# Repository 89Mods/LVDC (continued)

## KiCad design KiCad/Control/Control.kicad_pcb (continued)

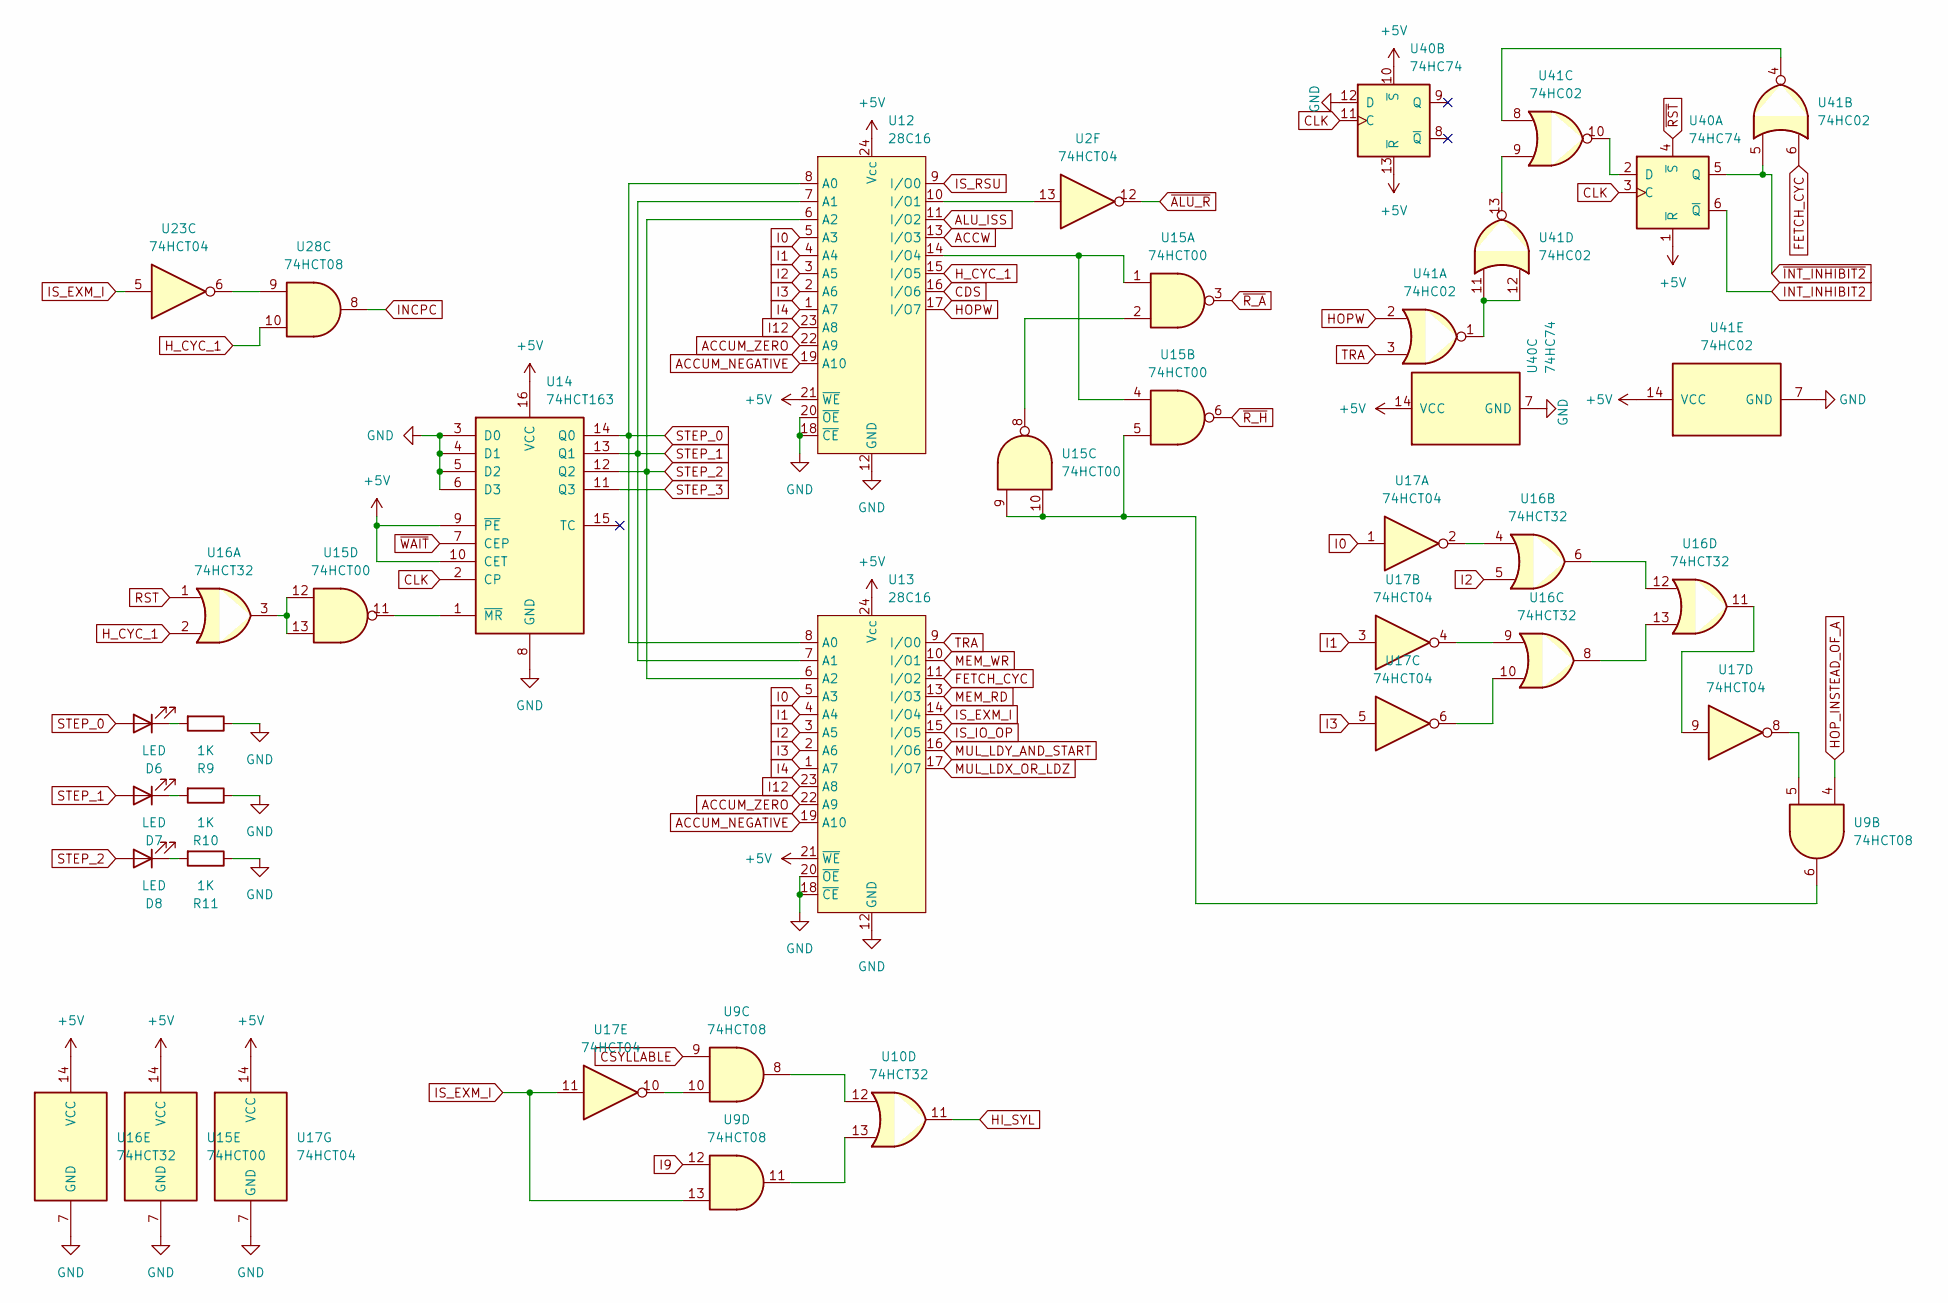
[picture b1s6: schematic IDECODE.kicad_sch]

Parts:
D6, D7, D8: LED; LED_1206_3216Metric_Pad1.42x1.75mm_HandSolder
R9, R10, R11: 1K; R_1206_3216Metric_Pad1.30x1.75mm_HandSolder
U2, U17, U23: 74HCT04; SO-14_3.9x8.65mm_P1.27mm
U9, U28: 74HCT08; SO-14_3.9x8.65mm_P1.27mm
U10, U16: 74HCT32; SO-14_3.9x8.65mm_P1.27mm
U12, U13: 28C16; DIP-24_W15.24mm_Socket
U14: 74HCT163; DIP-16_W7.62mm
U15: 74HCT00; SO-14_3.9x8.65mm_P1.27mm
U40: 74HC74; SO-14_3.9x8.65mm_P1.27mm
U41: 74HC02; SO-14_3.9x8.65mm_P1.27mm

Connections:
+5V: U12.21 (~WE), U12.24 (Vcc), U13.21 (~WE), U13.24 (Vcc), U14.9 (~PE), U14.10 (CET), U14.16 (VCC), U15.14 (VCC), U16.14 (VCC), U17.14 (VCC), U40.1 (~R), U40.10 (~S), U40.13 (~R), U40.14 (VCC), U41.14 (VCC); also elsewhere on the board
ACCUM_NEGATIVE: U12.19 (A10), U13.19 (A10); also elsewhere on the board
ACCUM_ZERO: U12.22 (A9), U13.22 (A9); also elsewhere on the board
ACCW: U12.13 (I/O3); also elsewhere on the board
ALU_ISS: U12.11 (I/O2); also elsewhere on the board
CDS: U12.16 (I/O6); also elsewhere on the board
CLK: U14.2 (CP), U40.3 (C), U40.11 (C); also elsewhere on the board
CSYLLABLE: U9.9; also elsewhere on the board
FETCH_CYC: U13.11 (I/O2), U41.6; also elsewhere on the board
GND: R9.1, R10.1, R11.1, U12.12 (GND), U12.18 (~CE), U12.20 (~OE), U13.12 (GND), U13.18 (~CE), U13.20 (~OE), U14.3 (D0), U14.4 (D1), U14.5 (D2), U14.6 (D3), U14.8 (GND), U15.7 (GND), U16.7 (GND), U17.7 (GND), U40.7 (GND), U40.12 (D), U41.7 (GND); also elsewhere on the board
HI_SYL: U10.11; also elsewhere on the board
HOPW: U12.17 (I/O7), U41.2; also elsewhere on the board
HOP_INSTEAD_OF_A: U9.4; also elsewhere on the board
H_CYC_1: U12.15 (I/O5), U16.2, U28.10; also elsewhere on the board
I0: U12.5 (A3), U13.5 (A3), U17.1; also elsewhere on the board
I1: U12.4 (A4), U13.4 (A4), U17.3; also elsewhere on the board
I2: U12.3 (A5), U13.3 (A5), U16.5; also elsewhere on the board
I3: U12.2 (A6), U13.2 (A6), U17.5; also elsewhere on the board
I4: U12.1 (A7), U13.1 (A7); also elsewhere on the board
I9: U9.12; also elsewhere on the board
I12: U12.23 (A8), U13.23 (A8); also elsewhere on the board
INCPC: U28.8; also elsewhere on the board
INT_INHIBIT2: U40.6 (~Q); also elsewhere on the board
IS_EXM_I: U9.13, U13.14 (I/O4), U17.11, U23.5; also elsewhere on the board
IS_IO_OP: U13.15 (I/O5); also elsewhere on the board
IS_RSU: U12.9 (I/O0); also elsewhere on the board
MEM_RD: U13.13 (I/O3); also elsewhere on the board
MEM_WR: U13.10 (I/O1); also elsewhere on the board
MUL_LDX_OR_LDZ: U13.17 (I/O7); also elsewhere on the board
MUL_LDY_AND_START: U13.16 (I/O6); also elsewhere on the board
unnamed: D6.1 (K), R9.2
unnamed: D7.1 (K), R10.2
unnamed: D8.1 (K), R11.2
unnamed: U9.8, U10.12
unnamed: U9.11, U10.13
unnamed: U2.13, U12.10 (I/O1)
unnamed: U12.14 (I/O4), U15.1, U15.4
unnamed: U14.1 (~MR), U15.11
unnamed: U15.2, U15.8
unnamed: U9.6, U15.5, U15.9, U15.10
unnamed: U15.12, U15.13, U16.3
unnamed: U16.4, U17.2
unnamed: U16.9, U17.4
unnamed: U16.10, U17.6
unnamed: U16.11, U17.9
unnamed: U16.6, U16.12
unnamed: U16.8, U16.13
unnamed: U9.5, U17.8
unnamed: U9.10, U17.10
unnamed: U23.6, U28.9
unnamed: U40.2 (D), U41.10
unnamed: U41.1, U41.11, U41.12
unnamed: U41.4, U41.8
unnamed: U41.9, U41.13
RST: U16.1; also elsewhere on the board
STEP_0: D6.2 (A), U12.8 (A0), U13.8 (A0), U14.14 (Q0)
STEP_1: D7.2 (A), U12.7 (A1), U13.7 (A1), U14.13 (Q1)
STEP_2: D8.2 (A), U12.6 (A2), U13.6 (A2), U14.12 (Q2); also elsewhere on the board
STEP_3: U14.11 (Q3)
TRA: U13.9 (I/O0), U41.3; also elsewhere on the board
~ALU_R: U2.12; also elsewhere on the board
~INT_INHIBIT2: U40.5 (Q), U41.5
~RST: U40.4 (~S); also elsewhere on the board
~R_A: U15.3; also elsewhere on the board
~R_H: U15.6; also elsewhere on the board
~WAIT: U14.7 (CEP); also elsewhere on the board

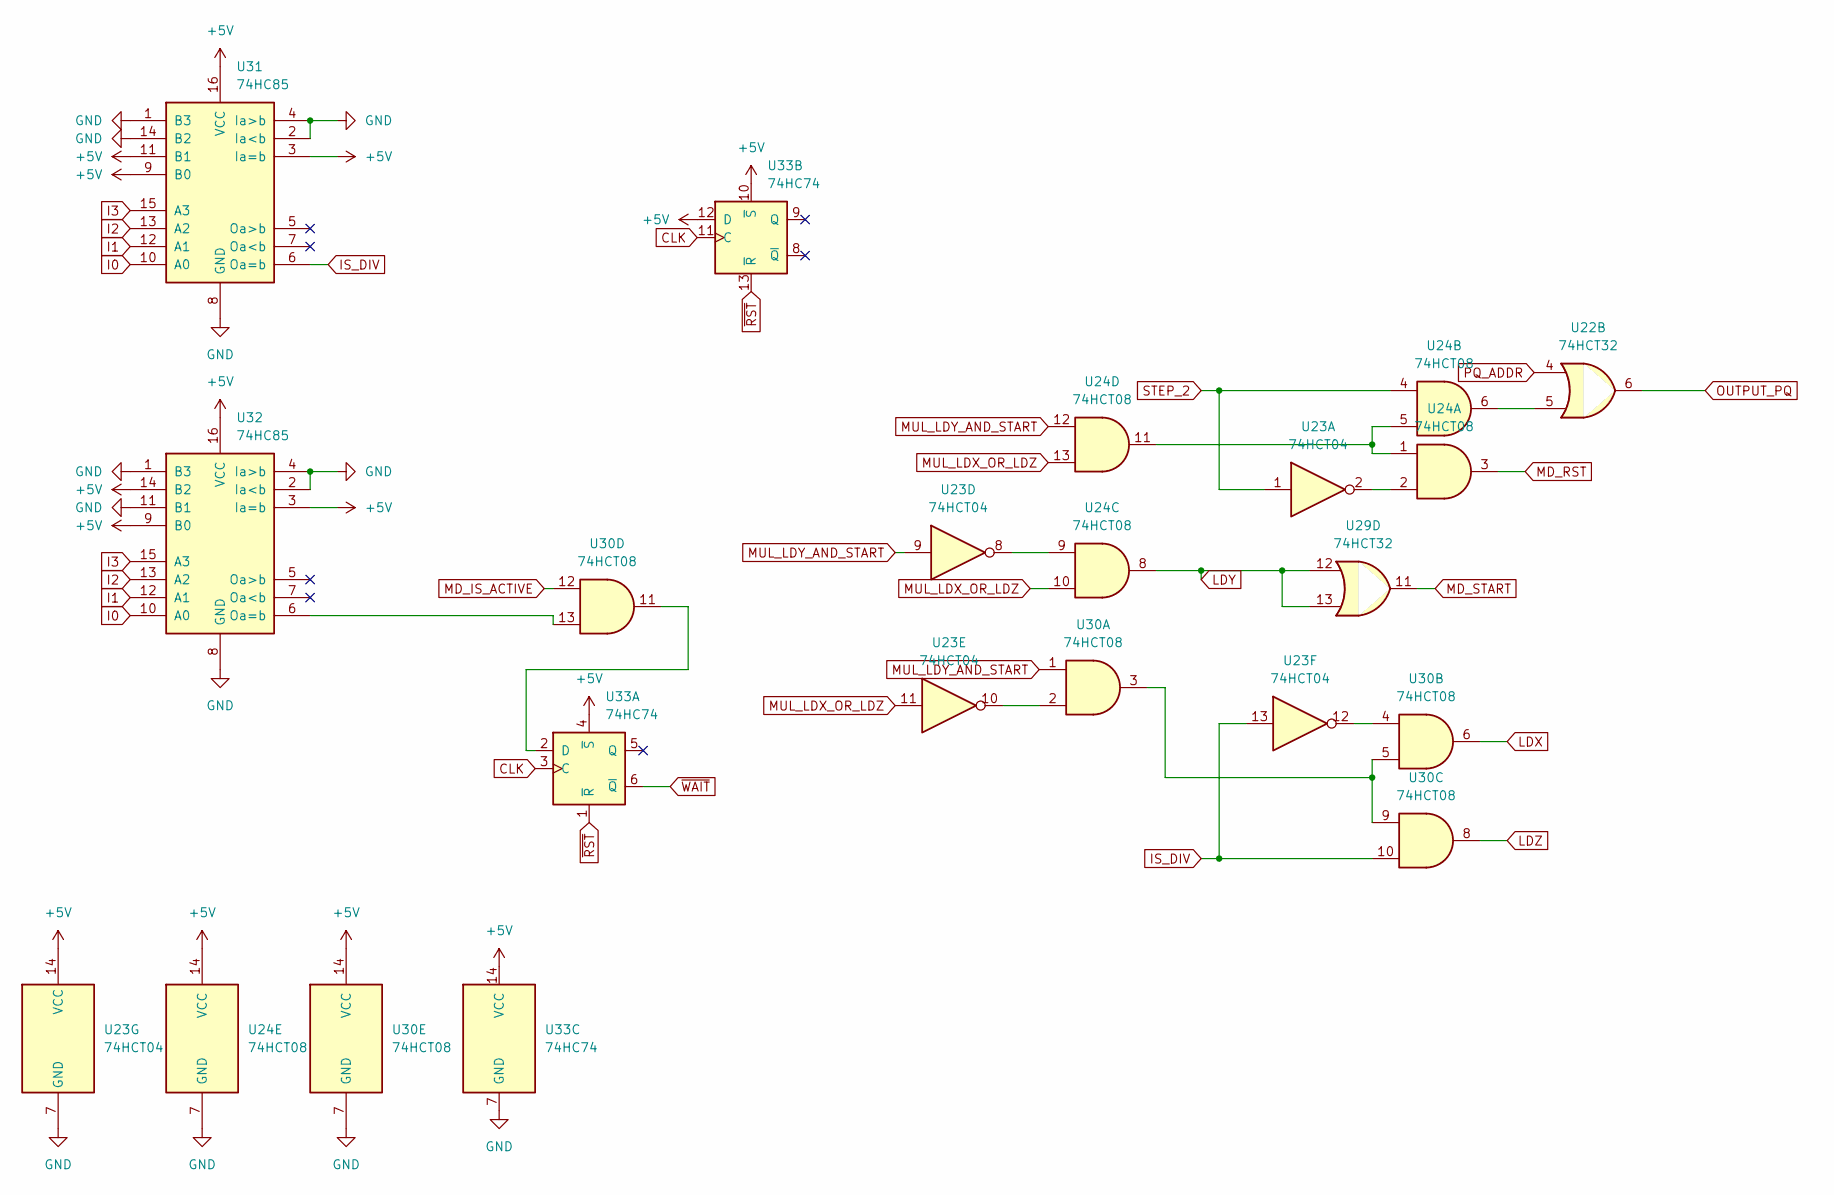
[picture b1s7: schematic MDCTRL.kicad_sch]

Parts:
U22, U29: 74HCT32; SO-14_3.9x8.65mm_P1.27mm
U23: 74HCT04; SO-14_3.9x8.65mm_P1.27mm
U24, U30: 74HCT08; SO-14_3.9x8.65mm_P1.27mm
U31, U32: 74HC85; DIP-16_W7.62mm
U33: 74HC74; SO-14_3.9x8.65mm_P1.27mm

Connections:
+5V: U23.14 (VCC), U24.14 (VCC), U30.14 (VCC), U31.3 (Ia=b), U31.9 (B0), U31.11 (B1), U31.16 (VCC), U32.3 (Ia=b), U32.9 (B0), U32.14 (B2), U32.16 (VCC), U33.4 (~S), U33.10 (~S), U33.12 (D), U33.14 (VCC); also elsewhere on the board
CLK: U33.3 (C), U33.11 (C); also elsewhere on the board
GND: U23.7 (GND), U24.7 (GND), U30.7 (GND), U31.1 (B3), U31.2 (Ia<b), U31.4 (Ia>b), U31.8 (GND), U31.14 (B2), U32.1 (B3), U32.2 (Ia<b), U32.4 (Ia>b), U32.8 (GND), U32.11 (B1), U33.7 (GND); also elsewhere on the board
I0: U31.10 (A0), U32.10 (A0); also elsewhere on the board
I1: U31.12 (A1), U32.12 (A1); also elsewhere on the board
I2: U31.13 (A2), U32.13 (A2); also elsewhere on the board
I3: U31.15 (A3), U32.15 (A3); also elsewhere on the board
IS_DIV: U23.13, U30.10, U31.6 (Oa=b); also elsewhere on the board
LDX: U30.6; also elsewhere on the board
LDY: U24.8, U29.12, U29.13; also elsewhere on the board
LDZ: U30.8; also elsewhere on the board
MD_IS_ACTIVE: U30.12; also elsewhere on the board
MD_RST: U24.3; also elsewhere on the board
MD_START: U29.11; also elsewhere on the board
MUL_LDX_OR_LDZ: U23.11, U24.10, U24.13; also elsewhere on the board
MUL_LDY_AND_START: U23.9, U24.12, U30.1; also elsewhere on the board
unnamed: U22.5, U24.6
unnamed: U23.2, U24.2
unnamed: U23.8, U24.9
unnamed: U23.10, U30.2
unnamed: U23.12, U30.4
unnamed: U24.1, U24.5, U24.11
unnamed: U30.3, U30.5, U30.9
unnamed: U30.13, U32.6 (Oa=b)
unnamed: U30.11, U33.2 (D)
OUTPUT_PQ: U22.6; also elsewhere on the board
PQ_ADDR: U22.4; also elsewhere on the board
STEP_2: U23.1, U24.4; also elsewhere on the board
~RST: U33.1 (~R), U33.13 (~R); also elsewhere on the board
~WAIT: U33.6 (~Q); also elsewhere on the board

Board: 4 copper layers, 81 parts (0 on the bottom side), 202 nets, no tracks yet.

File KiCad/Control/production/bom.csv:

Designator,Footprint,Quantity,Value,LCSC Part #
"C1, C10, C11, C12, C13, C7, C8, C9",0805,8,100nF,
"C2, C3, C4, C5, C6",CP_Radial_D4.0mm_P2.00mm,5,10µF,
"D1, D2, D3, D4, D5, D6, D7, D8",1206,8,LED,
J1,PinHeader_2x22_P2.54mm_Vertical,1,TO_BACKPLANE,
J2,PinHeader_2x04_P2.54mm_Vertical,1,TO_ALU,
J3,PinHeader_2x06_P2.54mm_Vertical,1,TO_MEMORY,
J4,PinHeader_2x06_P2.54mm_Vertical,1,TO_REGISTERS,
J5,PinHeader_2x04_P2.54mm_Vertical,1,TO_MULDIV,
"J6, J7, J8",PinHeader_1x01_P2.54mm_Vertical,3,Conn_01x01,
"R1, R10, R11, R2, R6, R8, R9",1206,7,1K,
R3,1206,1,4.7K,
"R4, R5, R7",1206,3,15K,
"U1, U7",SO-20_12.8x7.5mm_P1.27mm,2,74HC574,
"U10, U16, U22, U29",SO-14_3.9x8.65mm_P1.27mm,4,74HCT32,
"U11, U21, U24, U25, U28, U30, U9",SO-14_3.9x8.65mm_P1.27mm,7,74HCT08,
"U12, U13",DIP-24_W15.24mm_Socket,2,28C16,
U14,DIP-16_W7.62mm,1,74HCT163,
U15,SO-14_3.9x8.65mm_P1.27mm,1,74HCT00,
"U17, U2, U23",SO-14_3.9x8.65mm_P1.27mm,3,74HCT04,
"U18, U19, U26, U27",SO-14_3.9x8.65mm_P1.27mm,4,74HCT74,
"U20, U3, U36, U37, U38, U39, U4, U5, U6, U8",SO-16_3.9x9.9mm_P1.27mm,10,74HCT157,
"U31, U32",DIP-16_W7.62mm,2,74HC85,
U33,SO-14_3.9x8.65mm_P1.27mm,1,74HC74,
U34,SO-20_12.8x7.5mm_P1.27mm,1,74HC688,
U35,SO-14_3.9x8.65mm_P1.27mm,1,74HC00,

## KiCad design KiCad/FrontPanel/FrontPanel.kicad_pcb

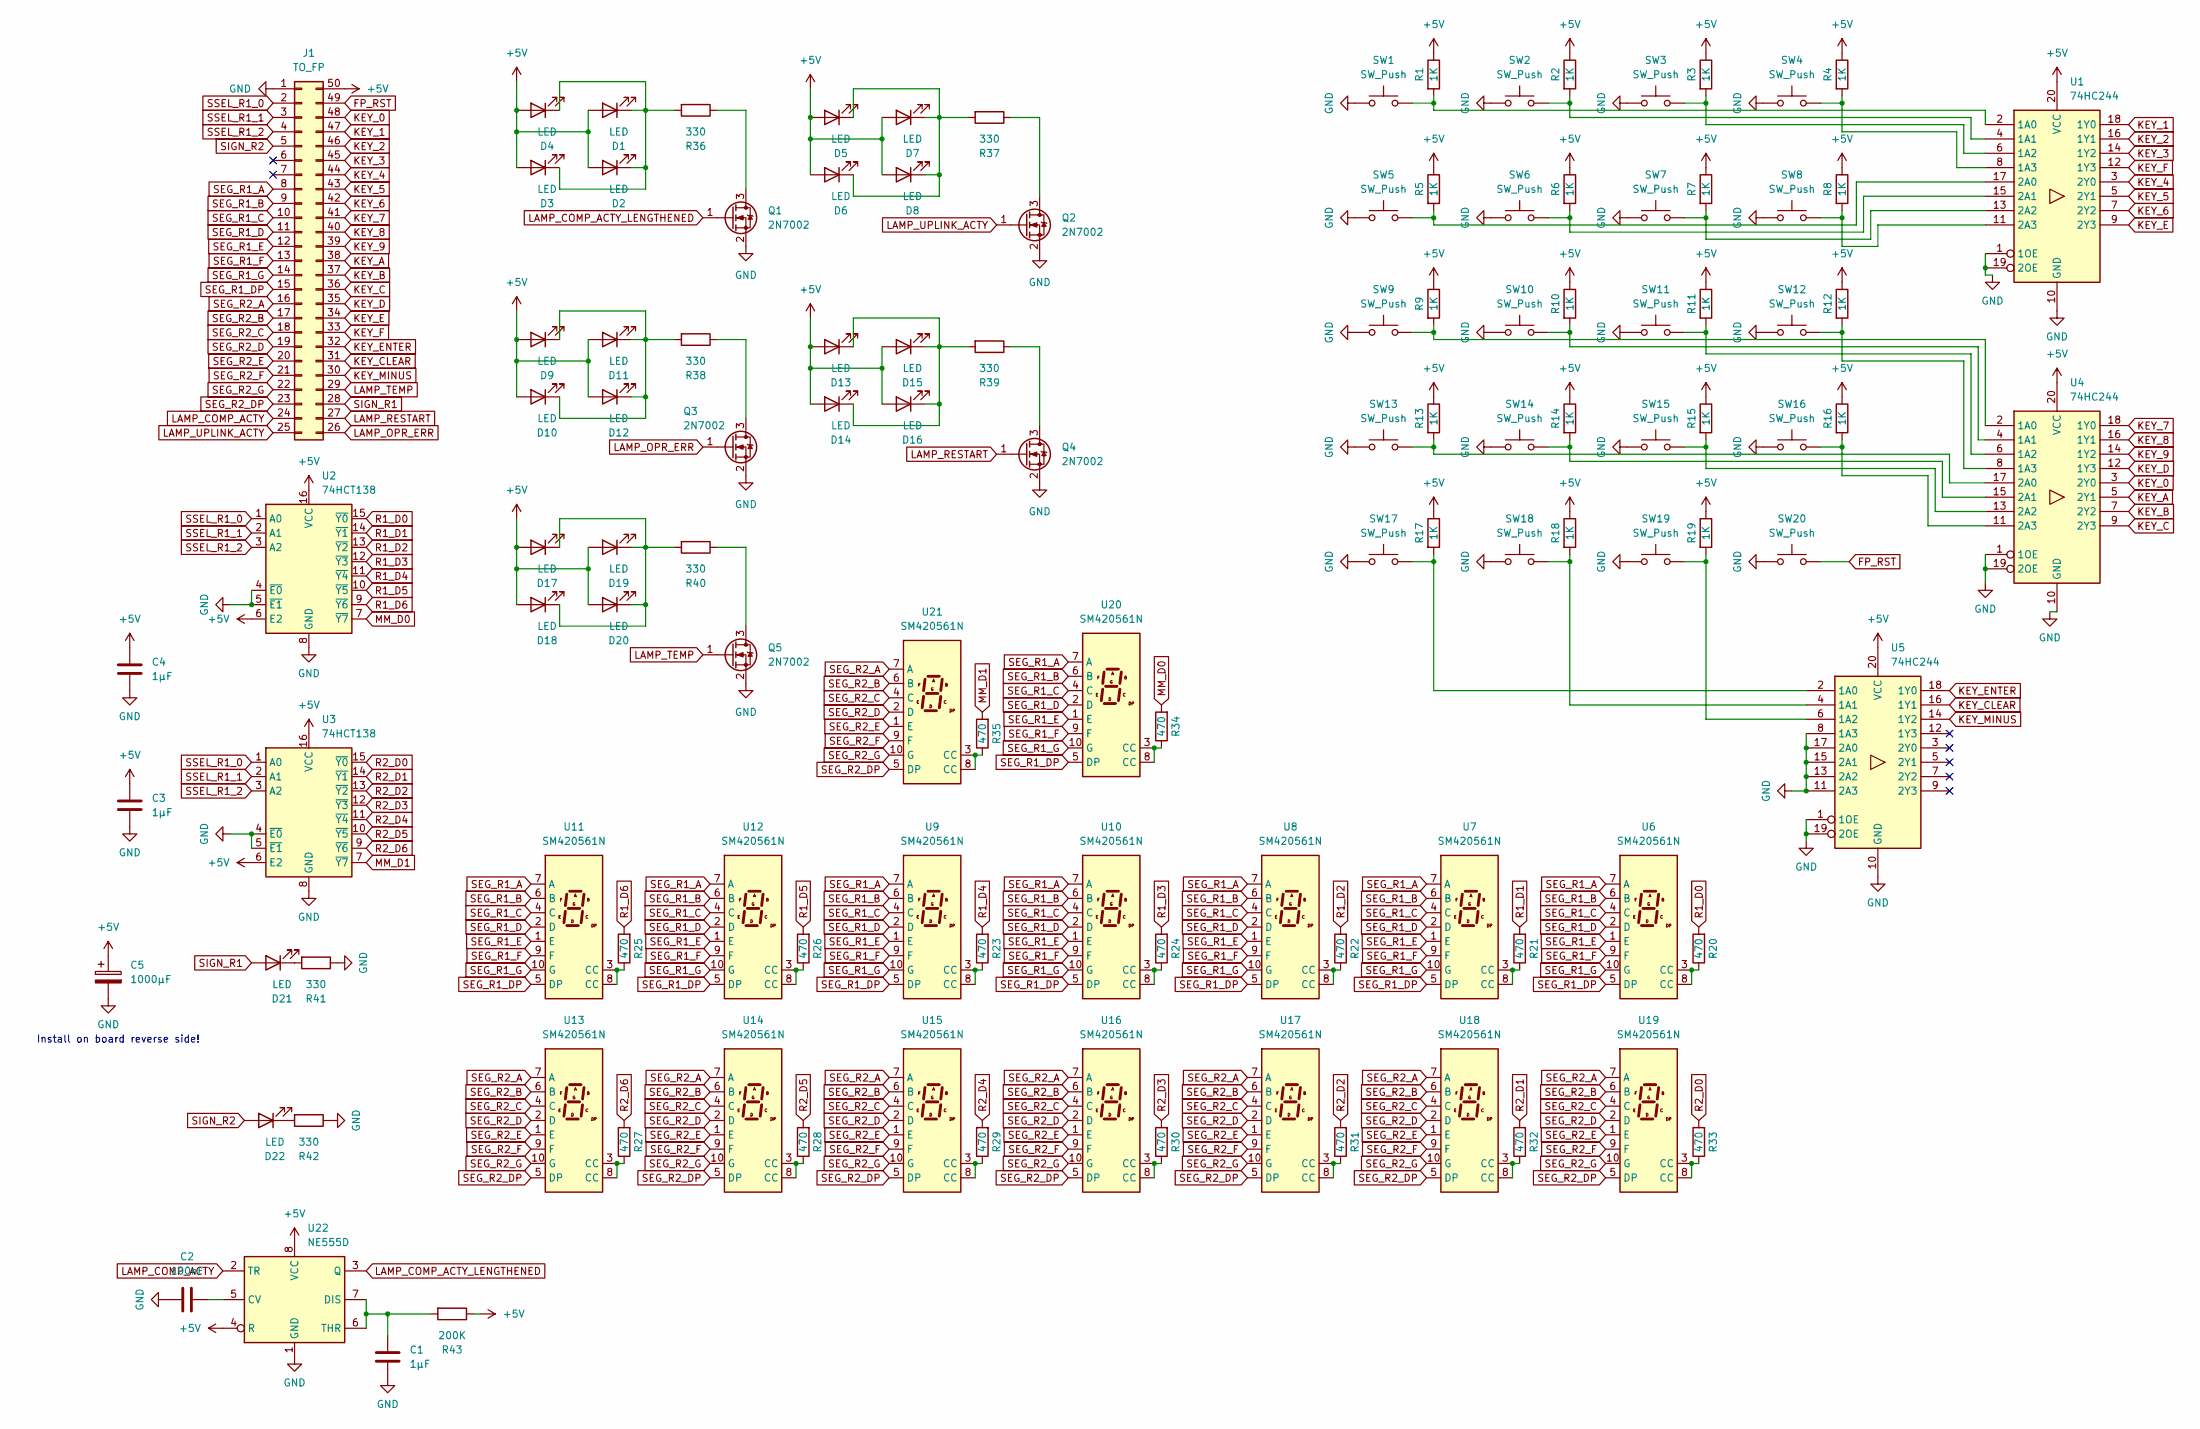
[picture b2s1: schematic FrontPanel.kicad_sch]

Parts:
C1, C3, C4: 1µF; C_0805_2012Metric_Pad1.18x1.45mm_HandSolder
C2: 100nF; C_0805_2012Metric_Pad1.18x1.45mm_HandSolder
C5: 1000µF; CP_Radial_D6.3mm_P2.50mm
D1, D2, D3, D4, D5, D6, D7, D8, D9, D10, D11, D12, D13, D14, D15, D16, D17, D18, D19, D20: LED; LED_1206_3216Metric_Pad1.42x1.75mm_HandSolder
D21, D22: LED; LED_D5.0mm
J1: TO_FP; PinHeader_2x25_P2.54mm_Vertical
Q1, Q2, Q3, Q4, Q5: 2N7002; SOT-23
R1, R2, R3, R4, R5, R6, R7, R8, R9, R10, R11, R12, R13, R14, R15, R16, R17, R18, R19: 1K; R_1206_3216Metric_Pad1.30x1.75mm_HandSolder
R20, R21, R22, R23, R24, R25, R26, R27, R28, R29, R30, R31, R32, R33, R34, R35: 470; R_1206_3216Metric_Pad1.30x1.75mm_HandSolder
R36, R37, R38, R39, R40, R41, R42: 330; R_1206_3216Metric_Pad1.30x1.75mm_HandSolder
R43: 200K; R_1206_3216Metric_Pad1.30x1.75mm_HandSolder
SW1, SW2, SW3, SW4, SW5, SW6, SW7, SW8, SW9, SW10, SW11, SW12, SW13, SW14, SW15, SW16, SW17, SW18, SW19, SW20: SW_Push; SW_Cherry_MX_1.00u_PCB
U1, U4, U5: 74HC244; SO-20_12.8x7.5mm_P1.27mm
U2, U3: 74HCT138; SO-16_3.9x9.9mm_P1.27mm
U6, U7, U8, U9, U10, U11, U12, U13, U14, U15, U16, U17, U18, U19, U20, U21: SM420561N; 7SegmentLED_LTS6760_LTS6780
U22: NE555D; SOIC-8_3.9x4.9mm_P1.27mm

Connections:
+5V: C3.2, C4.2, C5.1, D1.2 (A), D2.2 (A), D3.2 (A), D4.2 (A), D5.2 (A), D6.2 (A), D7.2 (A), D8.2 (A), D9.2 (A), D10.2 (A), D11.2 (A), D12.2 (A), D13.2 (A), D14.2 (A), D15.2 (A), D16.2 (A), D17.2 (A), D18.2 (A), D19.2 (A), D20.2 (A), J1.50, R1.1, R2.1, R3.1, R4.1, R5.1, R6.1, R7.1, R8.1, R9.1, R10.1, R11.1, R12.1, R13.1, R14.1, R15.1, R16.1, R17.1, R18.1, R19.1, R43.1, U1.20 (VCC), U2.6 (E2), U2.16 (VCC), U3.6 (E2), U3.16 (VCC), U4.20 (VCC), U5.20 (VCC), U22.4 (R), U22.8 (VCC)
FP_RST: J1.49, SW20.2
GND: C1.1, C2.2, C3.1, C4.1, C5.2, J1.1, Q1.2 (S), Q2.2 (S), Q3.2 (S), Q4.2 (S), Q5.2 (S), R41.1, R42.1, SW1.1, SW2.1, SW3.1, SW4.1, SW5.1, SW6.1, SW7.1, SW8.1, SW9.1, SW10.1, SW11.1, SW12.1, SW13.1, SW14.1, SW15.1, SW16.1, SW17.1, SW18.1, SW19.1, SW20.1, U1.1 (1OE), U1.10 (GND), U1.19 (2OE), U2.4 (~E0), U2.5 (~E1), U2.8 (GND), U3.4 (~E0), U3.5 (~E1), U3.8 (GND), U4.1 (1OE), U4.10 (GND), U4.19 (2OE), U5.1 (1OE), U5.8 (1A3), U5.10 (GND), U5.11 (2A3), U5.13 (2A2), U5.15 (2A1), U5.17 (2A0), U5.19 (2OE), U22.1 (GND)
KEY_0: J1.48, U4.3 (2Y0)
KEY_1: J1.47, U1.18 (1Y0)
KEY_2: J1.46, U1.16 (1Y1)
KEY_3: J1.45, U1.14 (1Y2)
KEY_4: J1.44, U1.3 (2Y0)
KEY_5: J1.43, U1.5 (2Y1)
KEY_6: J1.42, U1.7 (2Y2)
KEY_7: J1.41, U4.18 (1Y0)
KEY_8: J1.40, U4.16 (1Y1)
KEY_9: J1.39, U4.14 (1Y2)
KEY_A: J1.38, U4.5 (2Y1)
KEY_B: J1.37, U4.7 (2Y2)
KEY_C: J1.36, U4.9 (2Y3)
KEY_CLEAR: J1.31, U5.16 (1Y1)
KEY_D: J1.35, U4.12 (1Y3)
KEY_E: J1.34, U1.9 (2Y3)
KEY_ENTER: J1.32, U5.18 (1Y0)
KEY_F: J1.33, U1.12 (1Y3)
KEY_MINUS: J1.30, U5.14 (1Y2)
LAMP_COMP_ACTY: J1.24, U22.2 (TR)
LAMP_COMP_ACTY_LENGTHENED: Q1.1 (G), U22.3 (Q)
LAMP_OPR_ERR: J1.26, Q3.1 (G)
LAMP_RESTART: J1.27, Q4.1 (G)
LAMP_TEMP: J1.29, Q5.1 (G)
LAMP_UPLINK_ACTY: J1.25, Q2.1 (G)
MM_D0: R34.2, U2.7 (~Y7)
MM_D1: R35.2, U3.7 (~Y7)
unnamed: D1.1 (K), D2.1 (K), D3.1 (K), D4.1 (K), R36.2
unnamed: D5.1 (K), D6.1 (K), D7.1 (K), D8.1 (K), R37.2
unnamed: D9.1 (K), D10.1 (K), D11.1 (K), D12.1 (K), R38.2
unnamed: D13.1 (K), D14.1 (K), D15.1 (K), D16.1 (K), R39.2
unnamed: D17.1 (K), D18.1 (K), D19.1 (K), D20.1 (K), R40.2
unnamed: D21.1 (K), R41.2
unnamed: D22.1 (K), R42.2
unnamed: Q1.3 (D), R36.1
unnamed: Q2.3 (D), R37.1
unnamed: Q3.3 (D), R38.1
unnamed: Q4.3 (D), R39.1
unnamed: Q5.3 (D), R40.1
unnamed: R20.1, U6.3 (CC), U6.8 (CC)
unnamed: R21.1, U7.3 (CC), U7.8 (CC)
unnamed: R22.1, U8.3 (CC), U8.8 (CC)
unnamed: R23.1, U9.3 (CC), U9.8 (CC)
unnamed: R24.1, U10.3 (CC), U10.8 (CC)
unnamed: R25.1, U11.3 (CC), U11.8 (CC)
unnamed: R26.1, U12.3 (CC), U12.8 (CC)
unnamed: R27.1, U13.3 (CC), U13.8 (CC)
unnamed: R28.1, U14.3 (CC), U14.8 (CC)
unnamed: R29.1, U15.3 (CC), U15.8 (CC)
unnamed: R30.1, U16.3 (CC), U16.8 (CC)
unnamed: R31.1, U17.3 (CC), U17.8 (CC)
unnamed: R32.1, U18.3 (CC), U18.8 (CC)
unnamed: R33.1, U19.3 (CC), U19.8 (CC)
unnamed: R34.1, U20.3 (CC), U20.8 (CC)
unnamed: R35.1, U21.3 (CC), U21.8 (CC)
unnamed: R1.2, SW1.2, U1.2 (1A0)
unnamed: R2.2, SW2.2, U1.4 (1A1)
unnamed: R3.2, SW3.2, U1.6 (1A2)
unnamed: R4.2, SW4.2, U1.8 (1A3)
unnamed: R5.2, SW5.2, U1.17 (2A0)
unnamed: R6.2, SW6.2, U1.15 (2A1)
unnamed: R7.2, SW7.2, U1.13 (2A2)
unnamed: R8.2, SW8.2, U1.11 (2A3)
unnamed: R9.2, SW9.2, U4.2 (1A0)
unnamed: R10.2, SW10.2, U4.4 (1A1)
unnamed: R11.2, SW11.2, U4.6 (1A2)
unnamed: R12.2, SW12.2, U4.8 (1A3)
unnamed: R13.2, SW13.2, U4.17 (2A0)
unnamed: R14.2, SW14.2, U4.15 (2A1)
unnamed: R15.2, SW15.2, U4.13 (2A2)
unnamed: R16.2, SW16.2, U4.11 (2A3)
unnamed: R17.2, SW17.2, U5.2 (1A0)
unnamed: R18.2, SW18.2, U5.4 (1A1)
unnamed: R19.2, SW19.2, U5.6 (1A2)
unnamed: C2.1, U22.5 (CV)
unnamed: C1.2, R43.2, U22.6 (THR), U22.7 (DIS)
R1_D0: R20.2, U2.15 (~Y0)
R1_D1: R21.2, U2.14 (~Y1)
R1_D2: R22.2, U2.13 (~Y2)
R1_D3: R24.2, U2.12 (~Y3)
R1_D4: R23.2, U2.11 (~Y4)
R1_D5: R26.2, U2.10 (~Y5)
R1_D6: R25.2, U2.9 (~Y6)
R2_D0: R33.2, U3.15 (~Y0)
R2_D1: R32.2, U3.14 (~Y1)
R2_D2: R31.2, U3.13 (~Y2)
R2_D3: R30.2, U3.12 (~Y3)
R2_D4: R29.2, U3.11 (~Y4)
R2_D5: R28.2, U3.10 (~Y5)
R2_D6: R27.2, U3.9 (~Y6)
SEG_R1_A: J1.8, U6.7 (A), U7.7 (A), U8.7 (A), U9.7 (A), U10.7 (A), U11.7 (A), U12.7 (A), U20.7 (A)
SEG_R1_B: J1.9, U6.6 (B), U7.6 (B), U8.6 (B), U9.6 (B), U10.6 (B), U11.6 (B), U12.6 (B), U20.6 (B)
SEG_R1_C: J1.10, U6.4 (C), U7.4 (C), U8.4 (C), U9.4 (C), U10.4 (C), U11.4 (C), U12.4 (C), U20.4 (C)
SEG_R1_D: J1.11, U6.2 (D), U7.2 (D), U8.2 (D), U9.2 (D), U10.2 (D), U11.2 (D), U12.2 (D), U20.2 (D)
SEG_R1_DP: J1.15, U6.5 (DP), U7.5 (DP), U8.5 (DP), U9.5 (DP), U10.5 (DP), U11.5 (DP), U12.5 (DP), U20.5 (DP)
SEG_R1_E: J1.12, U6.1 (E), U7.1 (E), U8.1 (E), U9.1 (E), U10.1 (E), U11.1 (E), U12.1 (E), U20.1 (E)
SEG_R1_F: J1.13, U6.9 (F), U7.9 (F), U8.9 (F), U9.9 (F), U10.9 (F), U11.9 (F), U12.9 (F), U20.9 (F)
SEG_R1_G: J1.14, U6.10 (G), U7.10 (G), U8.10 (G), U9.10 (G), U10.10 (G), U11.10 (G), U12.10 (G), U20.10 (G)
SEG_R2_A: J1.16, U13.7 (A), U14.7 (A), U15.7 (A), U16.7 (A), U17.7 (A), U18.7 (A), U19.7 (A), U21.7 (A)
SEG_R2_B: J1.17, U13.6 (B), U14.6 (B), U15.6 (B), U16.6 (B), U17.6 (B), U18.6 (B), U19.6 (B), U21.6 (B)
SEG_R2_C: J1.18, U13.4 (C), U14.4 (C), U15.4 (C), U16.4 (C), U17.4 (C), U18.4 (C), U19.4 (C), U21.4 (C)
SEG_R2_D: J1.19, U13.2 (D), U14.2 (D), U15.2 (D), U16.2 (D), U17.2 (D), U18.2 (D), U19.2 (D), U21.2 (D)
SEG_R2_DP: J1.23, U13.5 (DP), U14.5 (DP), U15.5 (DP), U16.5 (DP), U17.5 (DP), U18.5 (DP), U19.5 (DP), U21.5 (DP)
SEG_R2_E: J1.20, U13.1 (E), U14.1 (E), U15.1 (E), U16.1 (E), U17.1 (E), U18.1 (E), U19.1 (E), U21.1 (E)
SEG_R2_F: J1.21, U13.9 (F), U14.9 (F), U15.9 (F), U16.9 (F), U17.9 (F), U18.9 (F), U19.9 (F), U21.9 (F)
SEG_R2_G: J1.22, U13.10 (G), U14.10 (G), U15.10 (G), U16.10 (G), U17.10 (G), U18.10 (G), U19.10 (G), U21.10 (G)
SIGN_R1: D21.2 (A), J1.28
SIGN_R2: D22.2 (A), J1.5
SSEL_R1_0: J1.2, U2.1 (A0), U3.1 (A0)
SSEL_R1_1: J1.3, U2.2 (A1), U3.2 (A1)
SSEL_R1_2: J1.4, U2.3 (A2), U3.3 (A2)

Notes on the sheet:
Install on board reverse side!

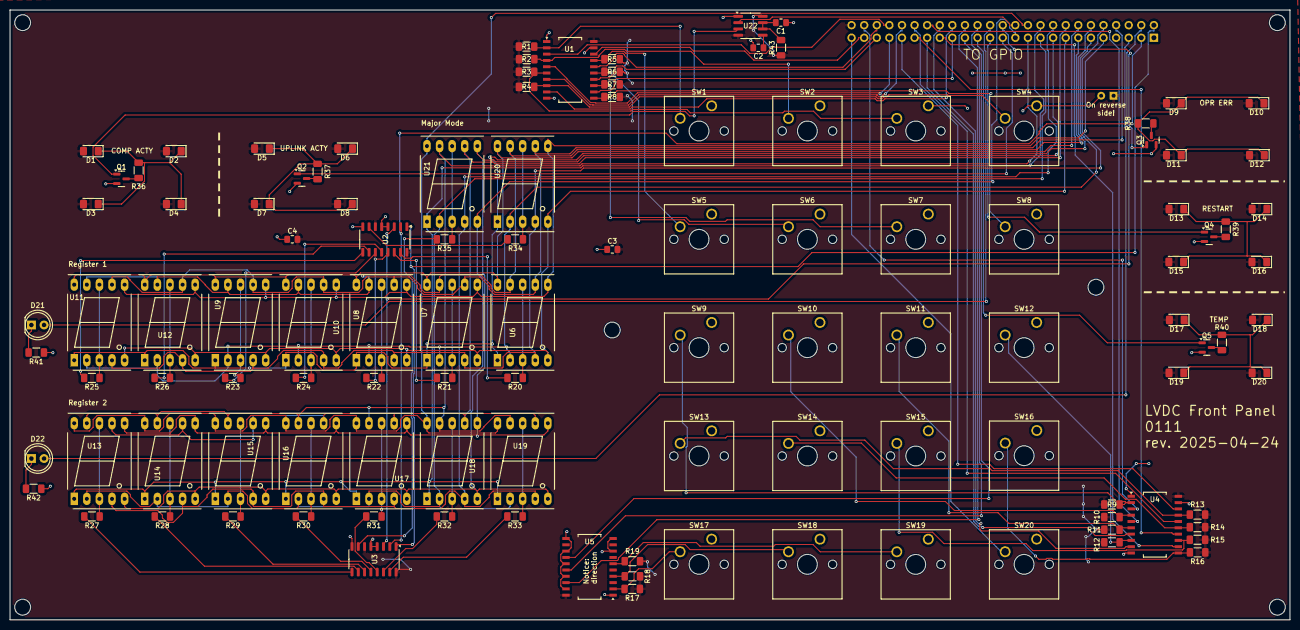
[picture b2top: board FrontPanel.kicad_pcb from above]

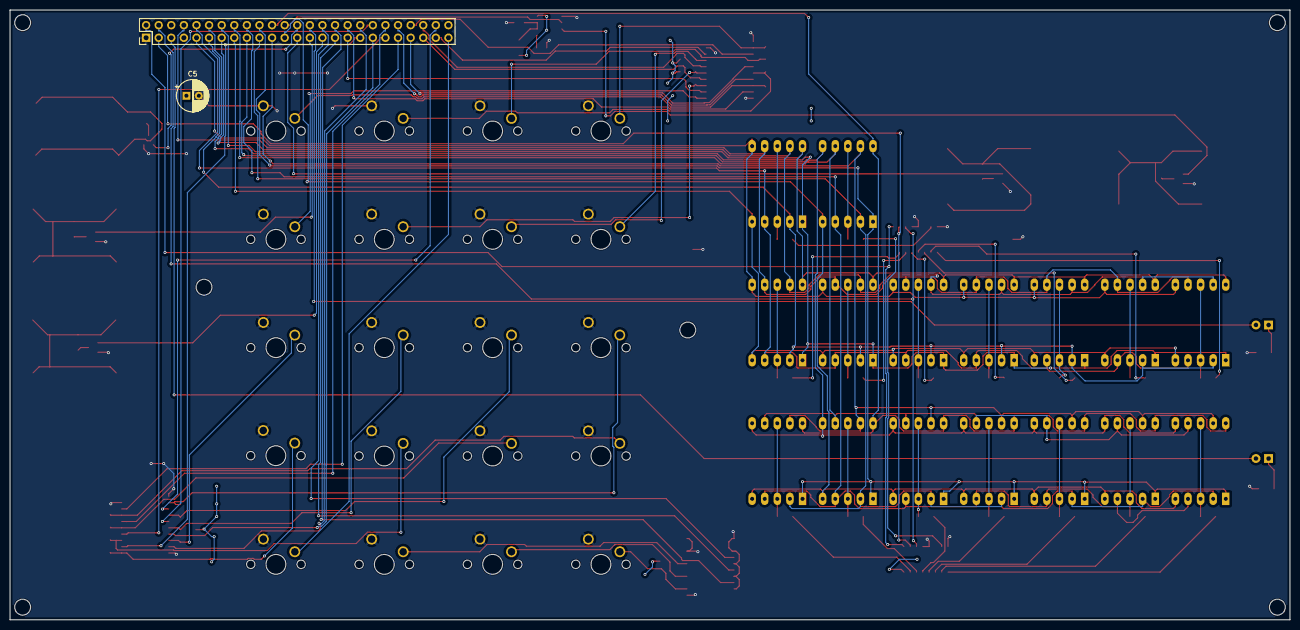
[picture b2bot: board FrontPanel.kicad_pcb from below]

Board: 2 copper layers, 258.1 x 122.9 mm, 118 parts (2 on the bottom side), 114 nets.

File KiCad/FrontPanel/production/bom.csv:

Designator,Footprint,Quantity,Value,LCSC Part #
"_6, _5, _4, _3, _2, ",,6,,
"C1, C3, C4",0805,3,1µF,
C2,0805,1,100nF,
C5,CP_Radial_D6.3mm_P2.50mm,1,1000µF,
"D1, D10, D11, D12, D13, D14, D15, D16, D17, D18, D19, D2, D20, D3, D4, D5, D6, D7, D8, D9",1206,20,LED,
"D21, D22",LED_D5.0mm,2,LED,
J1,PinHeader_2x25_P2.54mm_Vertical,1,TO_FP,
"Q1, Q2, Q3, Q4, Q5",SOT-23,5,2N7002,
"R1, R10, R11, R12, R13, R14, R15, R16, R17, R18, R19, R2, R3, R4, R5, R6, R7, R8, R9",1206,19,1K,
"R20, R21, R22, R23, R24, R25, R26, R27, R28, R29, R30, R31, R32, R33, R34, R35",1206,16,470,
"R36, R37, R38, R39, R40, R41, R42",1206,7,330,
R43,1206,1,200K,
"SW1, SW10, SW11, SW12, SW13, SW14, SW15, SW16, SW17, SW18, SW19, SW2, SW20, SW3, SW4, SW5, SW6, SW7, SW8, SW9",SW_Cherry_MX_1.00u_PCB,20,SW_Push,
"U1, U4, U5",SO-20_12.8x7.5mm_P1.27mm,3,74HC244,
"U10, U11, U12, U13, U14, U15, U16, U17, U18, U19, U20, U21, U6, U7, U8, U9",7SegmentLED_LTS6760_LTS6780,16,SM420561N,
"U2, U3",SO-16_3.9x9.9mm_P1.27mm,2,74HCT138,
U22,SOIC-8_3.9x4.9mm_P1.27mm,1,NE555D,
